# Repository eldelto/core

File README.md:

# Mono-repo for Personal Projects

This repository contains most of the things I'm currently working on
plus a bunch of helper libraries.

It contains the following somewhat finished projects:

## keyd-x11-application-mapper

Drop-in replacement for [keyd-application-mapper](https://github.com/rvaiya/keyd/blob/master/scripts/keyd-application-mapper).

Please see the project's [README](/cmd/keyd-x11-application-mapper/README.org) for more
information.

## Flake Finder

A CLI tool to identify flaky tests or flaky command behaviour in
general.

Please see the project's [README](/cmd/flake-finder/README.md) for more
information.

## Worklog

A CLI tool so automate work time bookings to Jira Tempo and Personio.

Please see the project's [README](/cmd/worklog/README.md) for more
information.

## Solvent

Efficient, self-hostable, no-fuzz to-do list with magic-link login and
list sharing.

Please see the project's [README](/cmd/solvent/README.md) for more
information.

## Diatom

A Forth-like language implementation that runs on its own stack VM
with a custom assembler. The VM implementation exist for Go and
Javascript.

Please see the project's [README](/cmd/diatom/README.md) for more
information.

## Riff Robot

A small website that suggests random scales and chords every day for
guitar practice.

Please see the project's [README](/cmd/riffrobot/README.md) for more
information.

## Plant Guild

A small website to help you in choosing beneficial neighbours for your
next planting project.

Please see the project's [README](/cmd/plantguild/README.md) for more
information.

## Blog

My personal blog that uses an Org-Mode file as CMS. Currently hosted
at [www.eldelto.net](https://www.eldelto.net).

Please see the project's [README](/cmd/blog/README.md) for more
information.

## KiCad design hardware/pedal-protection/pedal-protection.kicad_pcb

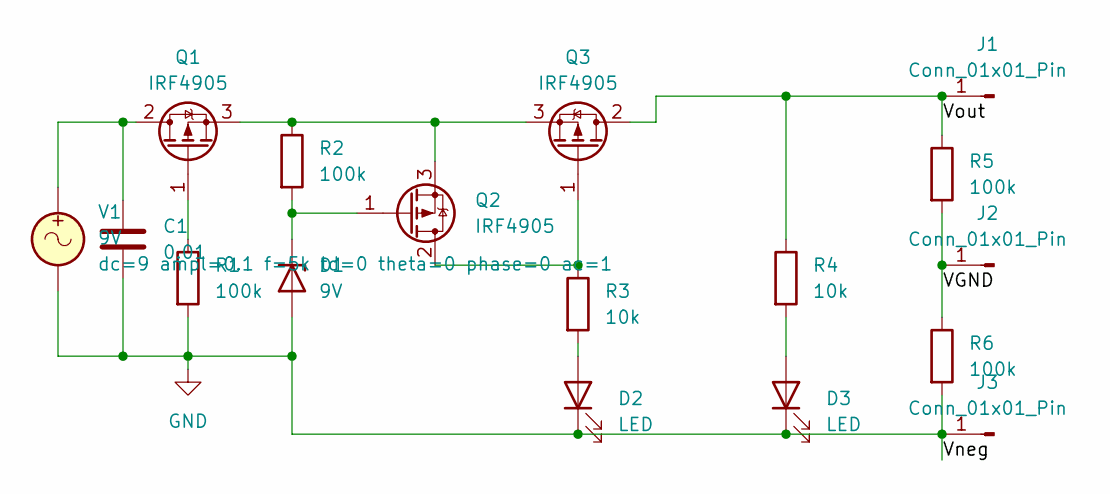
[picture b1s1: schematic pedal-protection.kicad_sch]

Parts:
C1: 0.01; C_Disc_D5.0mm_W2.5mm_P5.00mm
D1: 9V; D_DO-41_SOD81_P10.16mm_Horizontal
D2, D3: LED; LED_D3.0mm
J1, J2, J3: Conn_01x01_Pin; SolderWirePad_1x01_SMD_2x4mm
Q1, Q2, Q3: IRF4905; TO-220-3_Vertical
R1, R2, R5, R6: 100k; R_Axial_DIN0204_L3.6mm_D1.6mm_P2.54mm_Vertical
R3, R4: 10k; R_Axial_DIN0204_L3.6mm_D1.6mm_P2.54mm_Vertical
V1: 9V; R_2010_5025Metric_Pad1.40x2.65mm_HandSolder

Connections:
/VGND: J2.1, R5.2, R6.1
/Vout: J1.1, Q3.2 (D), R4.1, R5.1
GND: C1.2, D1.2 (A), D2.1 (K), D3.1 (K), J3.1, R1.2, R6.2, V1.2
unnamed: D1.1 (K), Q2.1 (G), R2.2
unnamed: D2.2 (A), R3.2
unnamed: D3.2 (A), R4.2
unnamed: C1.1, Q1.2 (D), V1.1
unnamed: Q1.1 (G), R1.1
unnamed: Q1.3 (S), Q2.3 (S), Q3.3 (S), R2.1
unnamed: Q2.2 (D), Q3.1 (G), R3.1

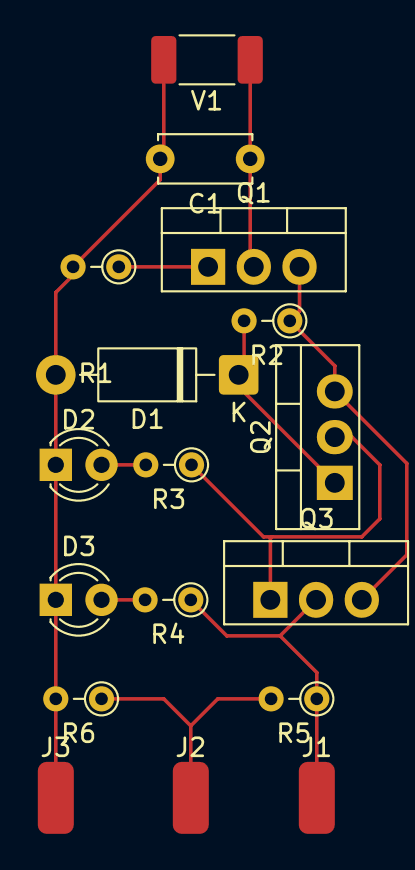
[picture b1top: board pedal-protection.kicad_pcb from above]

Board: 2 copper layers, 17 parts (0 on the bottom side), 10 nets.

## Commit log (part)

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2024-03-19 Add READMEs with TODOs
2024-03-20 Plant Guild: Add copy button
2024-03-20 Fix failing tests
2024-03-23 Draw background image
2024-03-24 Finish up Plant Guild CSS
2024-03-24 Make whole page scrollable
2024-03-24 Fix breaking change
2024-03-25 Fix some CSS
2024-03-25 Test find word and enhance stack trace
2024-03-28 Make repl lunch from CLI tool
2024-03-29 Test 'create' word
2024-03-29 Test more compilation words
2024-03-30 Support constants in compiled words
2024-04-01 Add plant guild screenshot
2024-04-01 Fix links
2024-04-01 Add rel-me link to Github
2024-04-05 Support block quotes
2024-04-05 Support ordered lists
2024-04-06 Add more microformat properties to the article page
2024-04-09 Refactor Diatom CLI tools
2024-04-10 Load stdlib when starting repl
2024-04-14 Add blues scales to random scale generator
2024-04-15 Create todos for the next steps
2024-04-16 Prepare Diatom stdlib tests
2024-04-17 Implement "'" word
2024-04-20 Add hirajoshi scale
2024-04-20 Add new scale to random pool
2024-04-22 Implement 'literal'
2024-04-23 Implement 0branch
2024-04-23 Implement 0branch and branch
2024-04-23 Improve blog inline replacements
2024-04-23 Fix blog title escaping
2024-04-24 Implement [compile]
2024-04-24 Start implementing branching words
2024-04-25 More experiments
2024-04-26 Introduce 'ref' and 'postpone'
2024-04-26 Implement 'else'
2024-04-28 Fix blog tests
2024-04-28 Make the blog somewhat fully managed by a single Org-Mode file
2024-04-29 Make tests pass
2024-04-29 Use template controller as fallback
2024-04-30 Implement 'recurse' & 'return'
2024-05-01 Fix sitemap generation
2024-05-01 Remove unused images
2024-05-02 Start implementing higher-level looping constructs
2024-05-03 Rename looping construct
2024-05-03 Kick-off Solvent rewrite
2024-05-03 Implement basic editing functionality
2024-05-03 Test conditionals
2024-05-03 Implement factorial
2024-05-04 Implement text patch parsing
2024-05-05 Enable blog page compression
2024-05-05 Test Solvent list patch logic
2024-05-05 Update dependencies
2024-05-06 Fix 'times' word
2024-05-07 Kick-off Diatom Javascript port
2024-05-08 Implement Stack class
2024-05-09 Implement solvent data migrator
2024-05-10 Cross out completed to-do lists
2024-05-13 Prepare Solvent service benchmark
2024-05-14 More Javascript VM implemenation
2024-05-15 Implement memory fetch methods
2024-05-15 Improve list editing
2024-05-17 Implement first Diatom JS tests
2024-05-17 Implement more Diatom JS instructions
2024-05-21 Implement more instructions
2024-05-24 Resolving the main word from the dictionary
2024-05-24 Support dumping/loading the VM memory content
2024-05-24 Implement 'key' instruction
2024-05-25 Fix layout for mobile devices
2024-05-25 Solvent: More layout cleanup
2024-05-27 Diatom: Kick-off custom web component for browser REPL
2024-05-28 Blog: Prepare browser Diatom execution
2024-05-30 Blog: Support raw HTML
2024-06-03 Diatom: Implement browser REPL
2024-06-04 Diatom remove unused comments
2024-06-07 Solvent: Various small fixes
2024-06-08 Solvent: Properly merge notebooks before storing
2024-06-09 Solvent: Add JS for adding single items
2024-06-09 Solvent: Implement single item deletion
2024-06-09 Solvent: Add missing init call
2024-06-10 Solvent: Cancel long press on move
2024-06-10 Solvent: Remove ordering and fix long-press
2024-06-10 Solvent: Inline checkmark icon
2024-06-11 Solvent: Add more icons
2024-06-12 Solvent: Implement sorting
2024-06-12 Solvent: Start submitting all item states at once
2024-06-12 Diatom: Add extension function interface
2024-06-14 Solvent: Restructure list page
2024-06-14 Solvent: Fix linting errors
2024-06-17 Diatom: Implement extension function support
2024-06-17 Solvent: Improve CSS
2024-06-18 Solvent: Finish up list details page
2024-06-19 Solvent: More CSS and more icons
2024-06-21 Solvent: Cleanup CSS
2024-06-21 Solvent: Fix Sortables initialization
2024-06-23 Money-Penny: Implement basic OFX parsing
2024-06-25 Solvent: Display dialog on error response
2024-06-27 Solvent: Prettier error dialog
2024-06-28 Solvent: Start CRDT reimplementation
2024-06-28 Upgrade dependencies
2024-06-29 Solvent: Add tests to new CRDT
2024-07-02 Solvent: Rework core logic
2024-07-03 Solvent: Implement more controller logic
2024-07-05 Solvent: Implement text patch
2024-07-05 Moneypenny: Add copy button
2024-07-08 Solvent: Implement item deletion
2024-07-10 Solvent: Implement remaining controller actions
2024-07-11 Solvent: Implement migration tool
2024-07-29 Solvent: Fix sortable bug and add test case
2024-07-29 Solvent: Fix textarea autosizing
2024-07-31 Solvent: Use OOB swaps when list state changes
2024-07-31 Solvent: Implement cache-busting
2024-08-01 Solvent: Work on cache-busting implementation
2024-08-02 MoneyPenny: Add more filters and fix presentation
2024-08-02 Solvent: Skip caching headers if no hash is present
2024-08-02 MoneyPenny: Fix failing test
2024-08-05 Sandi hat viele Fragen
2024-08-06 Solvent: Start implementing auth
2024-08-07 Solvent: Wire auth controller
2024-08-09 Solvent: Implement in-memory auth
2024-08-09 Solvent: Cleanup
2024-08-11 Solvent: Implement BBolt session store
2024-08-14 Downgrade required Go version
2024-08-14 Solvent: Implement env parsing helpers
2024-08-15 Solvent: Implement token E-mail sending
2024-08-16 Solvent: Implement list migration tool
2024-08-16 Solvent: Print host on startup
2024-08-16 Solvent: Increase cookie expiry time
2024-08-16 Solvent: Add favicon
2024-08-16 Solvent: Update favicon
2024-08-16 alles fertiggestellt
2024-08-16 css und html erstellt
2024-08-17 Riddle Club: Setup
2024-08-17 mit css grid herumgespielt
2024-08-23 Solvent: Make it runnable without SMTP setup
2024-08-23 Implement global template messages
2024-08-25 Riddle Club: Add SVG tiles
2024-08-27 Solvent: Implement list share POC
2024-08-27 Solvent: Don't force redirects in the auth middleware
2024-08-28 Solvent: Overhault authentication
2024-08-31 Riddle Club: Generate tile map
2024-09-01 ✨Tiles modifiziert, damit sie schön angezeigt werden ✨
2024-09-01 Solvent: POC to show shared lists on the home page
2024-09-02 Solvent: Improve the 404 page
2024-09-02 Blog: Fix templates
2024-09-02 Riddle Club: Fill all tiles
2024-09-03 Solvent: Style login pages
2024-09-03 Solvent: Add webmanifest
2024-09-04 Solvent: Use SVG favicon
2024-09-04 Solvent: Fix entry point
2024-09-04 Riddle Club: Implement logic edge-cases 🤖
2024-09-06 Solvent: Add edit dialog
2024-09-09 Solvent: Various little styling fixes
2024-09-10 Solvent: Style login E-mail
2024-09-11 💤Heute haben wir den ComboCounter hinzugefügt. Sandi schläft fast ein, als sie programmiert. Wieso macht mich programmieren immer so müde? Weil es sehr anstregend für meine Konzentration ist.💤
2024-09-13 Solvent: Write README
2024-09-14 Solvent: Finish up landing page
2024-09-14 Solvent: Make images larger
2024-09-17 Solvent: Properly sort shared to-do lists
2024-09-20 webdriver: Kick-off
2024-09-21 webdriver: Implement session creation
2024-09-27 Time-Sync: Automate Personio login via Microsoft
2024-09-27 Add persistent config storage
2024-10-04 Time-Sync: Get attendance data from personio
2024-10-04 TimeSync: Implement source detection and port clockify client
2024-10-05 Worklog: Wire Jire sink
2024-10-05 Worklog: Remove markdown support
2024-10-15 Worklog: Add more flags
2024-10-15 Worklog: Improve Personio sync
2024-10-16 Worklog: Figure out proper Personio sync
2024-10-17 Worklog: Remove dead code
2024-10-18 Worklog: Finish first implementation
2024-10-18 Worklog: Add readme
2024-10-18 Webdriver: Increase retry for FindElement
2024-10-18 WIP Solvent: Allow auth code to be entered manually
2024-10-18 Solvent: Support manual verification token entry
2024-10-24 Worklog: Don't skip over entries without ticket numbers
2024-10-25 Blog: Implement basic view tracking
2024-10-26 Worklog: Make syncing more generic
2024-11-09 Add projects to root README
2024-11-12 Worklog: Parallelize Jira updates
2024-11-26 Add coupling capacitor
2024-12-22 Add coupling capacitors
2025-01-06 Add alternate link pointing at the Atom feed
2025-01-27 Solvent: Extend session cookie life
2025-02-16 Solvent: Implement list deletion
2025-03-15 Diatom: Start V2 implementation
2025-03-15 Try out bolt db trigger functions
2025-03-15 Mealplanner: Make recipe persistence work
2025-03-16 CSS mit Chat-Bot-Hilfe :)
2025-03-16 Mealplanner: Implement basic meal plan
2025-03-16 Mealplanner: Use rationals for amount
2025-03-21 Mealplanner: Improve step parsing
2025-03-22 Mealplanner: Implement Wordpress parser
2025-03-22 Mealplanner: Improve Wordpress parsing
2025-03-24 Mealplanner: Implement recipe updates
2025-03-29 Opto-Comp: Draw circuit in LTspice
2025-04-01 OptoComp: Fix the amplifier section
2025-04-05 Mealplanner: Try out a new controller abstraction
2025-04-06 Buttons verändert
2025-04-09 Flake-Finder: Add README
2025-04-12 Mealplanner: Add category support
2025-04-13 OptoComp: Fix schematic errors
2025-04-15 Mealplanner: Implement basic meal plan feature
2025-04-22 Mealplanner: Fix recipe creation
2025-04-22 Mealplanner: Remove Println
2025-05-18 WIP support recipe sharing
2025-05-20 Worklog: Update attendance fetching
2025-05-21 Fix attendance creation
2025-05-26 Mealplanner: Support recipe sharing
2025-05-26 Support recipe share (#14)
    * WIP support recipe sharing
    * Mealplanner: Support recipe sharing
    ---------
2025-05-27 MealPlanner: Include shared recipes in suggestions
2025-05-30 Mealplanner: Fix share
2025-06-04 Bump golang.org/x/net from 0.37.0 to 0.38.0
    Bumps [golang.org/x/net](https://github.com/golang/net) from 0.37.0 to 0.38.0.
    - [Commits](https://github.com/golang/net/compare/v0.37.0...v0.38.0)
    ---
    updated-dependencies:
    - dependency-name: golang.org/x/net
    dependency-version: 0.38.0
2025-06-24 Fix assembler tests
2025-07-08 Diatom: Start array implementation
2025-07-18 Diatom: Continue array implementation
2025-07-19 Diatom: Finish array implementation
2025-07-23 Diatom: Implement number parsing
2025-07-24 Diatom: Implement word printing
2025-07-28 Diatom: Start number printing
2025-08-03 Diatom: Implement :array.equal?
2025-08-10 Diatom: More array functions
2025-08-16 Log-Luck: Initial setup
2025-08-17 Luck-Log: Fix login
2025-08-23 Diatom: Implement word flags
2025-08-24 Diatom: Implement word.find
2025-08-31 Diatom: Implement word compilation
2025-09-05 Worklog: Start Gitlab support
2025-09-07 Diatom: Add .string assembler macro
2025-11-08 Worklog: work on Gitlab sync
2025-11-10 Splitter pedal: Add protection circuit
2025-11-12 Worklog: more Gitlab syncing
2025-11-14 Worklog: fix race condition
2025-11-27 Worklog: Don't send empty body on GET requests
2025-12-21 Worklog: improve ticket regex
2025-12-26 Luck-log: implement end of year mail
2025-12-27 Luck-log: fix E-mail sending
2026-02-24 WIP support nested nodes in lists
2026-02-24 WIP improve parser
2026-03-01 React to window focus change
2026-03-04 Implement keyd-x11-application-mapper
2026-03-10 Prepare web refactor
2026-03-16 Make keyd-x11-application-mapper runnable as OpenRC service
2026-03-16 Switch to AGPL
2026-03-21 WIP implement new store functionality
2026-03-23 Implement Load
2026-03-24 Implement basic record diffing
2026-04-06 Implement ListAll
2026-04-18 worklog: Support Microsoft FIDO flow
2026-05-10 Switch to transaction based operations
2026-05-16 Start file share implementation
2026-05-19 file-share: implement basic download
2026-05-29 worklog: Support password-less FIDO flow
2026-06-01 file-share: implement basic keyboard navigation
2026-06-01 file-share: more shortcuts
2026-06-02 file-share: implement download
2026-06-05 file-share: implement multi-file upload and deletion
2026-06-07 file-share: implement basic login
2026-06-10 file-share: implement directory creation
2026-06-12 file-share: implement request cancelling
2026-06-12 file-share: progress card resetting
2026-06-14 solvent: fix css
2026-06-14 file-share: push missed service
2026-06-14 chore: run go fix
2026-06-15 file-share: more refactoring
2026-06-23 storage: refactoring
